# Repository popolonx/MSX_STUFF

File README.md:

# MSX_STUFF
This repository contains:
* Victor VHD IF-C9D replicated card
* NMS82XX front panel freecad files
* panasonic WX/WSX/turbo fdd adapter kicad files
* megaSCSI kicad files
* ToshibaHx34 related (firmware dump + some tcx2001 pinouts)
* etc

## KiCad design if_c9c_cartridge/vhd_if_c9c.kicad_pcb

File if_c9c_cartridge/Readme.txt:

VHD interface for cartridge slot in MSX 1
-Made from reverse engineering IF-C9D card.
-also contains pin headers to connect VHD data extraction pcb
-can be used to play games like Time Gal, Thunder Storm, Road Blaster where the game code is loaded from cassette tape.
-not possible to play games like VROOM and Star Arthur (even though the HW parts are now resolved) as game code is loaded from VHD disk itself and the code is in intermediate language that can be only interpreted by CALL VHD basic extension program.
-only full ROM dump from Victor IF-7900, IF-7910, IF-C9C, or National DA-80F is missing to be able to use CALL VHD basic extension (and thus play VROOM)

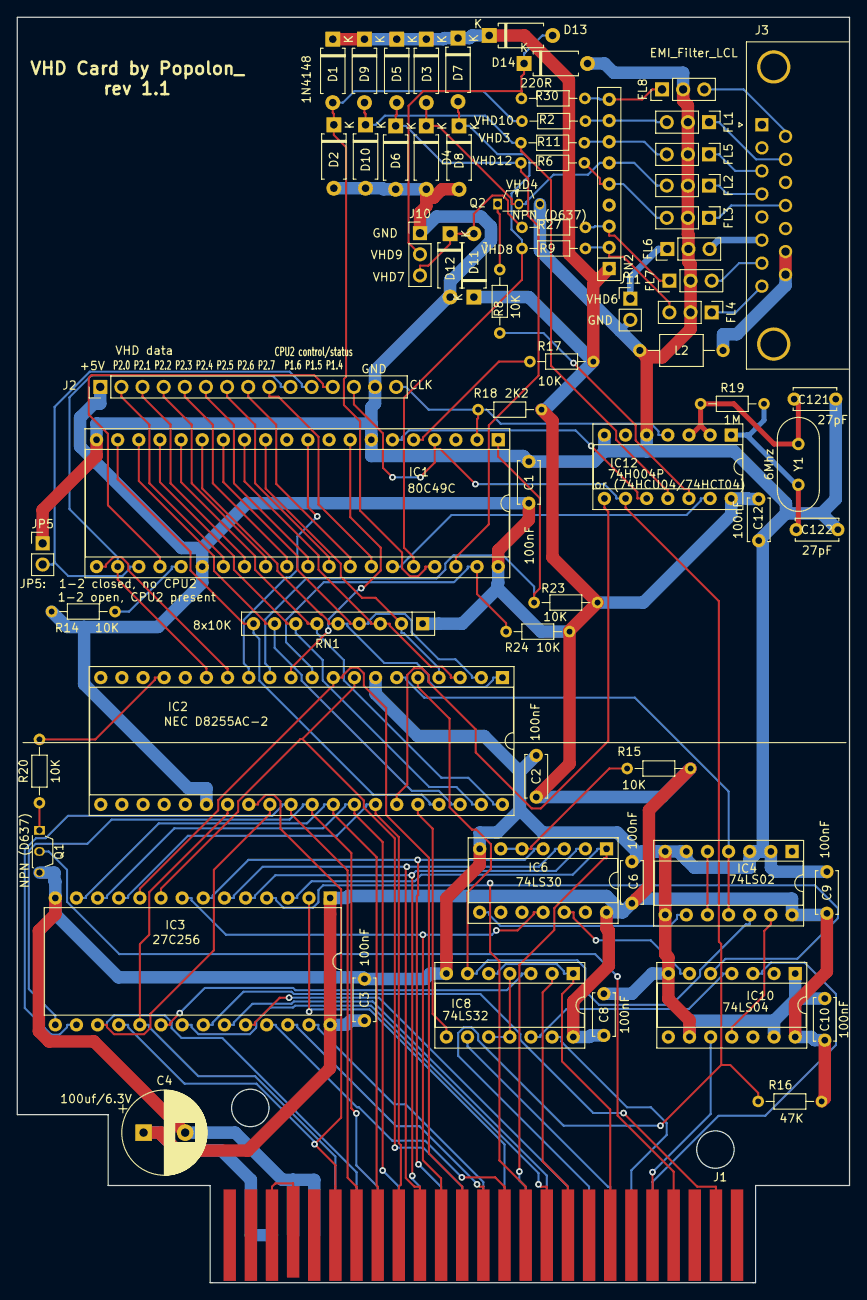
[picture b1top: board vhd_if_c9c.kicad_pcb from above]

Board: 2 copper layers, 100.0 x 152.0 mm, 69 parts (0 on the bottom side), 105 nets.

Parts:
C1, C2, C3, C6, C8, C9, C10, C12: 100nF; C_Disc_D5.0mm_W2.5mm_P5.00mm
C4: 100uf/6.3V; CP_Radial_D10.0mm_P5.00mm
C121, C122: 27pF; C_Disc_D5.0mm_W2.5mm_P5.00mm
D1, D2, D3, D4, D5, D6, D7, D8, D9, D10, D11, D12: 1N4148; D_A-405_P7.62mm_Horizontal
D13, D14: D; D_A-405_P7.62mm_Horizontal
FL1, FL2, FL3, FL4, FL5, FL6, FL7, FL8: EMI_Filter_LCL; PinHeader_1x03_P2.54mm_Vertical
IC1: 80C49C; DIP-40_W15.24mm_Socket
IC2: NEC D8255AC-2; DIP-40_W15.24mm_Socket
IC3: 27C256; DIP-28_W15.24mm
IC4: 74LS02; DIP-14_W7.62mm_Socket
IC6: 74LS30; DIP-14_W7.62mm_Socket
IC8: 74LS32; DIP-14_W7.62mm_Socket
IC10: 74LS04; DIP-14_W7.62mm_Socket
IC12: 74H004P; DIP-14_W7.62mm_Socket
J1: Conn_02x25_Odd_Even; msx_cartridge
J2: CONN_01x15; PinHeader_1x15_P2.54mm_Vertical
J3: DB15_Female; DSUB-15_Female_Horizontal_P2.77x2.84mm_EdgePinOffset7.70mm_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
J10: CONN_01x03; PinHeader_1x03_P2.54mm_Vertical
J11: CONN_01x02; PinHeader_1x02_P2.54mm_Vertical
JP5: Jumper; PinHeader_1x02_P2.54mm_Vertical
L2: L; L_Axial_L5.0mm_D3.6mm_P10.00mm_Horizontal_Murata_BL01RN1A2A2
Q1, Q2: NPN (D637); TO-92S_Wide
R2, R6, R9, R11, R27, R30: 220R; R_Axial_DIN0204_L3.6mm_D1.6mm_P7.62mm_Horizontal
R8, R14, R15, R17, R20, R23, R24: 10K; R_Axial_DIN0204_L3.6mm_D1.6mm_P7.62mm_Horizontal
R16: 47K; R_Axial_DIN0204_L3.6mm_D1.6mm_P7.62mm_Horizontal
R18: 2K2; R_Axial_DIN0204_L3.6mm_D1.6mm_P7.62mm_Horizontal
R19: 1M; R_Axial_DIN0204_L3.6mm_D1.6mm_P7.62mm_Horizontal
RN1: 8x10K; R_Array_SIP9
RN2: 8x4K7; R_Array_SIP9
Y1: 6Mhz; Crystal_HC18-U_Vertical

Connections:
5V: C1.1, C2.1, C3.1, C4.1, C6.1, C8.1, C9.1, C10.1, C12.1, D1.1, D3.1, D5.1, D7.1, D9.1, D11.1, D13.1, IC1.26, IC1.40, IC2.26, IC3.1, IC3.28, IC4.14, IC6.14, IC8.14, IC10.14, IC12.14, J1.45, J1.47, J2.1, R14.1, R15.1, R16.1, R17.1, R18.1, R23.1, R24.1, RN1.1, RN2.1
A0: IC2.9, IC3.10, J1.28
A1: IC2.8, IC3.9, J1.27
A2: IC3.8, IC6.11, J1.30
A3: IC3.7, IC6.4, J1.29
A4: IC3.6, IC6.3, J1.32
A5: IC3.5, IC6.2, J1.31
A6: IC3.4, IC10.5, J1.22
A7: IC3.3, IC6.1, J1.21
A8: IC3.25, J1.24
A9: IC3.24, J1.17
A10: IC3.21, J1.20
A11: IC3.23, J1.19
A12: IC3.2, J1.23
A13: IC3.26, J1.26
A14: IC3.27, J1.25
A15: IC8.2, J1.18
BUSDIR: IC10.10, J1.10
CLK: IC1.2, IC12.4, J2.15, R18.2
CPU2_P1.6: IC1.22, IC2.15, J2.10
D0: IC2.34, IC3.11, J1.34
D1: IC2.33, IC3.12, J1.33
D2: IC2.32, IC3.13, J1.36
D3: IC2.31, IC3.15, J1.35
D4: IC2.30, IC3.16, J1.38
D5: IC2.29, IC3.17, J1.37
D6: IC2.28, IC3.18, J1.40
D7: IC2.27, IC3.19, J1.39
GND: C1.2, C2.2, C3.2, C4.2, C6.2, C8.2, C9.2, C10.2, C12.2, C121.2, C122.2, D2.2, D4.2, D6.2, D8.2, D10.2, D12.2, D14.2, FL1.2, FL2.2, FL3.2, FL4.2, FL5.2, FL6.2, FL7.2, FL8.2, IC1.7, IC1.20, IC2.7, IC3.14, IC4.2, IC4.3, IC4.6, IC4.7, IC4.8, IC6.7, IC8.7, IC10.1, IC10.7, IC10.9, IC10.13, IC12.5, IC12.7, J1.41, J1.43, J2.14, J10.1, J11.2, JP5.1, L2.1, Q1.3, Q2.3
INT01_: J1.8, Q1.2
IOE_: IC8.13, J1.11
LIR_: IC10.3, J1.9
unnamed: C121.1, IC12.2, IC12.3, R19.1, Y1.1
unnamed: C122.1, IC12.1, R19.2, Y1.2
unnamed: D1.2, D2.1, IC1.37, R2.2
unnamed: D5.2, D6.1, IC1.38, R6.2
unnamed: D7.2, D8.1, IC1.36, R9.2
unnamed: D9.2, D10.1, IC12.11, R11.2
unnamed: FL6.3, J3.6
unnamed: FL7.3, J3.7
unnamed: IC1.5, R17.2
unnamed: IC1.6, IC12.10
unnamed: IC1.12, IC2.4, RN1.2
unnamed: IC1.13, IC2.3, RN1.3
unnamed: IC1.14, IC2.2, RN1.4
unnamed: IC1.15, IC2.1, RN1.5
unnamed: IC1.16, IC2.40, RN1.6
unnamed: IC1.17, IC2.39, RN1.7
unnamed: IC1.18, IC2.38, RN1.8
unnamed: IC1.19, IC2.37, RN1.9
unnamed: IC1.25, R14.2
unnamed: IC1.35, IC12.13
unnamed: IC2.5, IC4.12, IC8.6
unnamed: IC2.6, IC4.4, IC4.11
unnamed: IC2.17, R20.2
unnamed: IC2.36, IC8.8
unnamed: IC3.20, IC8.3
unnamed: IC4.9, IC6.8
unnamed: IC4.5, IC4.10
unnamed: IC6.5, IC6.6, R15.2
unnamed: IC8.4, IC8.10, IC8.11
unnamed: IC8.12, IC10.4
unnamed: IC6.12, IC10.6
unnamed: IC4.13, IC10.11
unnamed: IC2.35, IC12.8
unnamed: IC12.12, R8.2
unnamed: J1.44, J1.46
unnamed: J3.14, J3.15, L2.2
unnamed: Q1.1, R20.1
unnamed: Q2.1, R8.1
P1.0_CPU2_P2.0: IC1.27, J2.2
P1.1_CPU2_P2.1: IC1.28, J2.3
P1.2_CPU2_P2.2: IC1.29, J2.4
P1.3_CPU2_P2.3: IC1.30, J2.5
P1.4_CPU2_P2.4: IC1.31, J2.6
P1.5_CPU2_P2.5: IC1.32, J2.7
P1.6_CPU2_P2.6: IC1.33, J2.8
P1.7_CPU2_P2.7: IC1.34, J2.9
P2.0_PC0: IC1.21, IC2.14
P2.2_CPU2_P1.5: IC1.23, J2.11, JP5.2
P2.3_CPU2_P1.4: IC1.24, J2.12
P6: FL6.1, J11.1
P7: D11.2, D12.1, J10.3, R27.1
P9: D13.2, D14.1, J10.2, R30.1
RD_: IC8.1, IC8.5, J1.14
RD_PC6: IC1.8, IC2.11
RESET_: IC1.4, IC12.9, J1.15, J2.13, R16.2
SLOT_: IC3.22, J1.4
T0_PC5: IC1.1, IC2.12, R23.2
T1_PC7: IC1.39, IC2.10, R24.2
VHD3: FL5.1, J3.3
VHD3PULLUP: FL5.3, R11.1, RN2.7
VHD4: FL2.1, J3.4
VHD4PULLUP: D3.2, D4.1, FL2.3, Q2.2, RN2.6
VHD7PULLUP: FL7.1, R27.2, RN2.3
VHD8: FL4.1, J3.8
VHD8PULLUP: FL4.3, R9.1, RN2.2
VHD9: FL8.3, J3.9
VHD9PULLUP: FL8.1, R30.2, RN2.9
VHD10: FL1.1, J3.10
VHD10PULLUP: FL1.3, R2.1, RN2.8
VHD12: FL3.1, J3.12
VHD12PULLUP: FL3.3, R6.1, RN2.5
WR_: IC8.9, J1.13
WR_PC4: IC1.10, IC2.13

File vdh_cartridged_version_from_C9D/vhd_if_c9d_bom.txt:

"Source:"	"E:\msx\vhd_if_c9d_cartversion\vhd_if_c9d.sch"
"Date:"	"30.1.2023 19:45:37"
"Tool:"	"Eeschema (5.1.5)-3"
"Component Count:"	"58"
"Ref"	"Value"	"Part"	"Footprint"	"Description"	"Vendor"
"C1"	"100nF"	"agg-kicad:C"	"Capacitor_THT:C_Disc_D5.0mm_W2.5mm_P5.00mm"	""	""
"C2"	"100nF"	"agg-kicad:C"	"Capacitor_THT:C_Disc_D5.0mm_W2.5mm_P5.00mm"	""	""
"C3"	"100nF"	"agg-kicad:C"	"Capacitor_THT:C_Disc_D5.0mm_W2.5mm_P5.00mm"	""	""
"C4"	"100uf/6.3V"	"Device:CP"	"Capacitor_THT:CP_Radial_D10.0mm_P5.00mm"	"Polarized capacitor"	""
"C6"	"100nF"	"agg-kicad:C"	"Capacitor_THT:C_Disc_D5.0mm_W2.5mm_P5.00mm"	""	""
"C8"	"100nF"	"agg-kicad:C"	"Capacitor_THT:C_Disc_D5.0mm_W2.5mm_P5.00mm"	""	""
"C9"	"100nF"	"agg-kicad:C"	"Capacitor_THT:C_Disc_D5.0mm_W2.5mm_P5.00mm"	""	""
"C10"	"100nF"	"agg-kicad:C"	"Capacitor_THT:C_Disc_D5.0mm_W2.5mm_P5.00mm"	""	""
"C12"	"100nF"	"agg-kicad:C"	"Capacitor_THT:C_Disc_D5.0mm_W2.5mm_P5.00mm"	""	""
"C121"	"27pF"	"agg-kicad:C"	"Capacitor_THT:C_Disc_D5.0mm_W2.5mm_P5.00mm"	""	""
"C122"	"27pF"	"agg-kicad:C"	"Capacitor_THT:C_Disc_D5.0mm_W2.5mm_P5.00mm"	""	""
"D1"	"1N4148"	"agg-kicad:D"	"Diode_THT:D_A-405_P7.62mm_Horizontal"	"Diode"	""
"D2"	"1N4148"	"agg-kicad:D"	"Diode_THT:D_A-405_P7.62mm_Horizontal"	"Diode"	""
"D3"	"1N4148"	"agg-kicad:D"	"Diode_THT:D_A-405_P7.62mm_Horizontal"	"Diode"	""
"D4"	"1N4148"	"agg-kicad:D"	"Diode_THT:D_A-405_P7.62mm_Horizontal"	"Diode"	""
"D5"	"1N4148"	"agg-kicad:D"	"Diode_THT:D_A-405_P7.62mm_Horizontal"	"Diode"	""
"D6"	"1N4148"	"agg-kicad:D"	"Diode_THT:D_A-405_P7.62mm_Horizontal"	"Diode"	""
"D7"	"1N4148"	"agg-kicad:D"	"Diode_THT:D_A-405_P7.62mm_Horizontal"	"Diode"	""
"D8"	"1N4148"	"agg-kicad:D"	"Diode_THT:D_A-405_P7.62mm_Horizontal"	"Diode"	""
"D9"	"1N4148"	"agg-kicad:D"	"Diode_THT:D_A-405_P7.62mm_Horizontal"	"Diode"	""
"D10"	"1N4148"	"agg-kicad:D"	"Diode_THT:D_A-405_P7.62mm_Horizontal"	"Diode"	""
"FL1"	"EMI_Filter_LCL"	"Device:EMI_Filter_LCL"	"Connector_PinHeader_2.54mm:PinHeader_1x03_P2.54mm_Vertical"	"EMI T-filter (LCL)"	""
"FL2"	"EMI_Filter_LCL"	"Device:EMI_Filter_LCL"	"Connector_PinHeader_2.54mm:PinHeader_1x03_P2.54mm_Vertical"	"EMI T-filter (LCL)"	""
"FL3"	"EMI_Filter_LCL"	"Device:EMI_Filter_LCL"	"Connector_PinHeader_2.54mm:PinHeader_1x03_P2.54mm_Vertical"	"EMI T-filter (LCL)"	""
"FL4"	"EMI_Filter_LCL"	"Device:EMI_Filter_LCL"	"Connector_PinHeader_2.54mm:PinHeader_1x03_P2.54mm_Vertical"	"EMI T-filter (LCL)"	""
"FL5"	"EMI_Filter_LCL"	"Device:EMI_Filter_LCL"	"Connector_PinHeader_2.54mm:PinHeader_1x03_P2.54mm_Vertical"	"EMI T-filter (LCL)"	""
"FL6"	"EMI_Filter_LCL"	"Device:EMI_Filter_LCL"	"Connector_PinHeader_2.54mm:PinHeader_1x03_P2.54mm_Vertical"	"EMI T-filter (LCL)"	""
"FL7"	"EMI_Filter_LCL"	"Device:EMI_Filter_LCL"	"Connector_PinHeader_2.54mm:PinHeader_1x03_P2.54mm_Vertical"	"EMI T-filter (LCL)"	""
"IC1"	"P8749C"	"MCU_Intel:8049"	"Package_DIP:DIP-40_W15.24mm_Socket"	"MCS-48 8-bit Microcontroller, 2KB Mask ROM, 128B RAM, DIP-40"	""
"IC2"	"NEC D8255AC-2"	"Interface:8255A"	"Package_DIP:DIP-40_W15.24mm_Socket"	"Programmable Peripheral Interface, PDIP-40"	""
"IC3"	"27C256"	"Memory_EPROM:27C256"	"Package_DIP:DIP-28_W15.24mm"	"OTP EPROM 256 KiBit"	""
"IC6"	"74LS30"	"74xx:74LS30"	"Package_DIP:DIP-14_W7.62mm_Socket"	"8-input NAND"	""
"IC8"	"74LS32"	"74xx:74LS32"	"Package_DIP:DIP-14_W7.62mm_Socket"	"Quad 2-input OR"	""
"IC9"	"74LS02"	"74xx:74LS02"	"Package_DIP:DIP-14_W7.62mm_Socket"	"quad 2-input NOR gate"	""
"IC10"	"74LS04"	"74xx:74LS04"	"Package_DIP:DIP-14_W7.62mm_Socket"	"Hex Inverter"	""
"IC12"	"74H004P or 74HCU04"	"74xx:74HC04"	"Package_DIP:DIP-14_W7.62mm_Socket"	"Hex Inverter"	""
"J1"	"Conn_02x25_Odd_Even"	"Connector_Generic:Conn_02x25_Odd_Even"	"msx cartridge:msx_cartridge"	"Generic connector, double row, 02x25, odd/even pin numbering scheme (row 1 odd numbers, row 2 even numbers), script generated (kicad-library-utils/schlib/autogen/connector/)"	""
"J3"	"DB15_Female"	"Connector:DB15_Female"	"Connector_Dsub:DSUB-15_Female_Horizontal_P2.77x2.84mm_EdgePinOffset7.70mm_Housed_MountingHolesOffset9.12mm"	"15-pin female D-SUB connector (low-density/2 columns)"	""
"L2"	"L"	"agg-kicad:L"	"Inductor_THT:L_Axial_L5.0mm_D3.6mm_P10.00mm_Horizontal_Murata_BL01RN1A2A2"	""	""
"Q1"	"NPN (D637 or BC635)"	"Device:Q_NPN_BCE"	"Package_TO_SOT_THT:TO-92S_Wide"	"NPN transistor, base/collector/emitter"	""
"Q2"	"NPN (D637 or BC635)"	"Device:Q_NPN_BCE"	"Package_TO_SOT_THT:TO-92S_Wide"	"NPN transistor, base/collector/emitter"	""
"R2"	"220R"	"agg-kicad:R"	"Resistor_THT:R_Axial_DIN0204_L3.6mm_D1.6mm_P7.62mm_Horizontal"	""	""
"R6"	"220R"	"agg-kicad:R"	"Resistor_THT:R_Axial_DIN0204_L3.6mm_D1.6mm_P7.62mm_Horizontal"	""	""
"R8"	"10K"	"agg-kicad:R"	"Resistor_THT:R_Axial_DIN0204_L3.6mm_D1.6mm_P7.62mm_Horizontal"	""	""
"R9"	"220R"	"agg-kicad:R"	"Resistor_THT:R_Axial_DIN0204_L3.6mm_D1.6mm_P7.62mm_Horizontal"	""	""
"R11"	"220R"	"agg-kicad:R"	"Resistor_THT:R_Axial_DIN0204_L3.6mm_D1.6mm_P7.62mm_Horizontal"	""	""
"R14"	"10K"	"agg-kicad:R"	"Resistor_THT:R_Axial_DIN0204_L3.6mm_D1.6mm_P7.62mm_Horizontal"	""	""
"R15"	"10K"	"agg-kicad:R"	"Resistor_THT:R_Axial_DIN0204_L3.6mm_D1.6mm_P7.62mm_Horizontal"	""	""
"R16"	"47K"	"agg-kicad:R"	"Resistor_THT:R_Axial_DIN0204_L3.6mm_D1.6mm_P7.62mm_Horizontal"	""	""
"R17"	"10K"	"agg-kicad:R"	"Resistor_THT:R_Axial_DIN0204_L3.6mm_D1.6mm_P7.62mm_Horizontal"	""	""
"R18"	"2K2"	"agg-kicad:R"	"Resistor_THT:R_Axial_DIN0204_L3.6mm_D1.6mm_P7.62mm_Horizontal"	""	""
"R19"	"1M"	"agg-kicad:R"	"Resistor_THT:R_Axial_DIN0204_L3.6mm_D1.6mm_P7.62mm_Horizontal"	""	""
"R20"	"10K"	"agg-kicad:R"	"Resistor_THT:R_Axial_DIN0204_L3.6mm_D1.6mm_P7.62mm_Horizontal"	""	""
"R23"	"10K"	"agg-kicad:R"	"Resistor_THT:R_Axial_DIN0204_L3.6mm_D1.6mm_P7.62mm_Horizontal"	""	""
"R24"	"10K"	"agg-kicad:R"	"Resistor_THT:R_Axial_DIN0204_L3.6mm_D1.6mm_P7.62mm_Horizontal"	""	""
"RN1"	"8x10K"	"Device:R_Network08"	"Resistor_THT:R_Array_SIP9"	"8 resistor network, star topology, bussed resistors, small symbol"	""
"RN2"	"8x4K7"	"Device:R_Network08"	"Resistor_THT:R_Array_SIP9"	"8 resistor network, star topology, bussed resistors, small symbol"	""
"Y1"	"6Mhz"	"Device:Crystal"	"Crystal:Crystal_HC18-U_Vertical"	"Two pin crystal"	""

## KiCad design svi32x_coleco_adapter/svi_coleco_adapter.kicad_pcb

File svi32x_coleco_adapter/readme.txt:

SVI-603 colecovision adapter drawn from pdf schematics:
https://www.samdal.com/SVIDOCS/STM-F_SVI603.pdf
-coleco cartridge connector is using 2.54mm row spacing
-spectravideo side cartridge connector is using 5.08mm row spacing

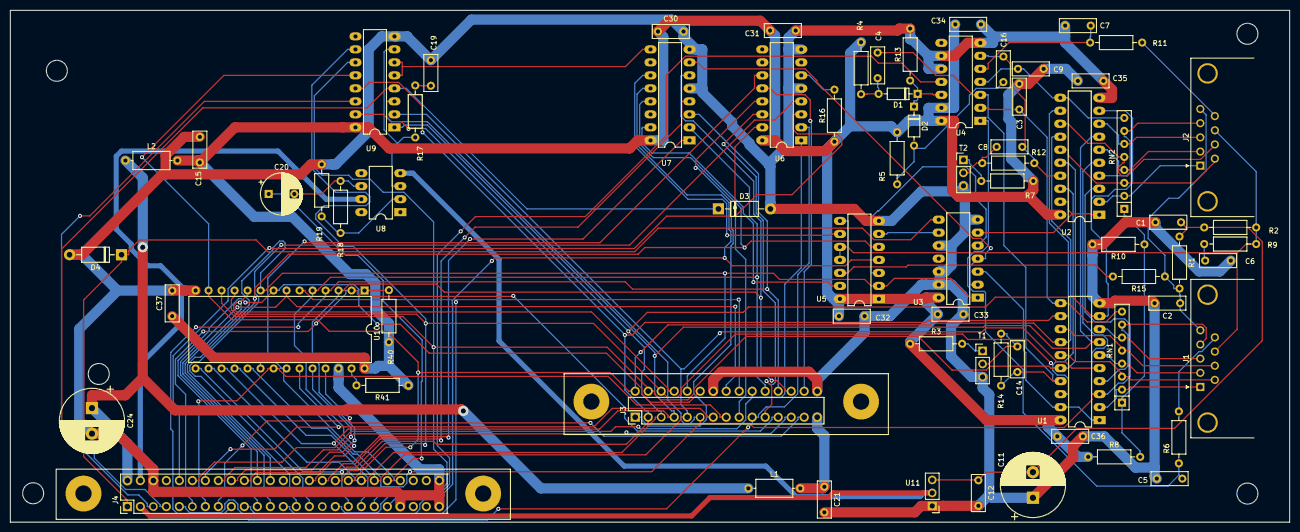
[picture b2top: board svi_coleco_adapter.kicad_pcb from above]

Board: 2 copper layers, 250.0 x 100.0 mm, 72 parts (0 on the bottom side), 93 nets.

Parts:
C1, C5, C7, C19, C30, C31, C32, C33, C34, C35, C36, C37: 100nf; C_Disc_D7.0mm_W2.5mm_P5.00mm
C2, C6: 10nf; C_Disc_D7.0mm_W2.5mm_P5.00mm
C3, C9: 1nF; C_Disc_D7.0mm_W2.5mm_P5.00mm
C4, C16: 10nF; C_Disc_D7.0mm_W2.5mm_P5.00mm
C8, C14: 100pF; C_Disc_D7.0mm_W2.5mm_P5.00mm
C11, C24: 100uf/16v; CP_Radial_D12.5mm_P5.00mm
C12: 100nF; C_Disc_D7.0mm_W2.5mm_P5.00mm
C15, C21: 2.2uf; C_Disc_D7.0mm_W2.5mm_P5.00mm
C20: 4.7uf/16v; CP_Radial_D8.0mm_P5.00mm
D1, D2: 1N4148; D_DO-35_SOD27_P7.62mm_Horizontal
D3: 1N4401; D_DO-41_SOD81_P10.16mm_Horizontal
D4: 1N4001; D_DO-41_SOD81_P10.16mm_Horizontal
J1, J2: Conn_01x09; DSUB-9_Male_Horizontal_P2.77x2.84mm_EdgePinOffset7.70mm_Hou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
J3: COLECO cartridge slot; COLECO_30_PIN_5_02
J4: SVI external bus connector; SVI_50PIN
L1, L2: L; L_Axial_L7.0mm_D3.3mm_P10.16mm_Horizontal_Fastron_MICC
R1, R2, R6, R11: 1K8; R_Axial_DIN0207_L6.3mm_D2.5mm_P10.16mm_Horizontal
R3, R7, R40, R41: 10K; R_Axial_DIN0207_L6.3mm_D2.5mm_P10.16mm_Horizontal
R4, R5: 100K; R_Axial_DIN0207_L6.3mm_D2.5mm_P10.16mm_Horizontal
R8, R10: 270R; R_Axial_DIN0207_L6.3mm_D2.5mm_P10.16mm_Horizontal
R9: 120; R_Axial_DIN0207_L6.3mm_D2.5mm_P10.16mm_Horizontal
R12, R14: 22K; R_Axial_DIN0207_L6.3mm_D2.5mm_P10.16mm_Horizontal
R13: 560R; R_Axial_DIN0207_L6.3mm_D2.5mm_P10.16mm_Horizontal
R15: 250; R_Axial_DIN0207_L6.3mm_D2.5mm_P10.16mm_Horizontal
R16: 3K3; R_Axial_DIN0207_L6.3mm_D2.5mm_P10.16mm_Horizontal
R17: 10R; R_Axial_DIN0207_L6.3mm_D2.5mm_P10.16mm_Horizontal
R18, R19: 2K2; R_Axial_DIN0207_L6.3mm_D2.5mm_P10.16mm_Horizontal
RN1, RN2: 22Kx7; R_Array_SIP8
T1, T2: NPN_CBE_BC547B (was 9014B); PinHeader_1x03_P2.54mm_Vertical
U1, U2: 74LS244; DIP-20_W7.62mm_LongPads
U3: 74LS32; DIP-14_W7.62mm_LongPads
U4, U5: 74LS00; DIP-14_W7.62mm_LongPads
U6, U7: 74LS138; DIP-16_W7.62mm_LongPads
U8: LM741; DIP-8_W7.62mm_LongPads
U9: SN76489; DIP-16_W7.62mm_LongPads
U10: 27C256; DIP-28_W15.24mm
U11: L79L05; PinHeader_1x03_P2.54mm_Vertical

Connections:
5V: C24.1, J4.1, L1.1, L2.1
5V_COL: C21.1, J3.30, L1.2
12V: J4.3, U8.7
+5V: C3.2, C9.2, C15.1, C30.1, C31.1, C32.1, C33.1, C34.1, C35.1, C36.1, C37.1, L2.2, R3.1, R4.1, R5.1, R7.1, R8.1, R16.1, R40.1, R41.1, U1.20, U2.20, U3.14, U4.13, U4.14, U5.1, U5.14, U6.16, U7.16, U9.16, U10.28
A0: J3.7, J4.24, U10.10
A1: J3.9, J4.23, U3.1, U5.2, U10.9
A2: J3.11, J4.22, U10.8
A3: J3.15, J4.21, U10.7
A4: J3.17, J4.20, U10.6
A5: J3.21, J4.19, U7.2, U10.5
A6: J3.23, J4.18, U7.3, U10.4
A7: J3.25, J4.17, U7.6, U10.3
A8: J3.28, J4.16, U10.25
A9: J3.26, J4.15, U10.24
A10: J3.16, J4.14, U10.21
A11: J3.14, J4.13, U10.23
A12: J3.24, J4.12, U10.2
A13: J3.19, J4.11, U6.1
A14: J3.20, J4.10, U6.2
A15: J4.9, U6.3
CLK: J4.8, U9.14
COL_JOY5: C2.1, J1.5, J2.5, R1.2, R15.1
COL_JOY8: J1.8, J2.8, R2.2, R9.1, U5.10, U5.11
CSOUND: C20.1, J4.41
CS_8000: J3.18, U6.15
CS_A000: J3.22, U6.14
CS_C000: J3.2, U6.13
CS_E000: J3.27, U6.12
D0: J3.5, J4.33, U1.18, U2.18, U9.10, U10.11
D1: J3.3, J4.34, U1.16, U2.16, U9.11, U10.12
D2: J3.1, J4.35, U1.14, U2.14, U9.12, U10.13
D3: J3.4, J4.36, U1.12, U2.12, U9.13, U10.15
D4: J3.6, J4.37, U1.9, U2.9, U9.15, U10.16
D5: J3.8, J4.38, U1.7, U2.7, U9.1, U10.17
D6: J3.10, J4.39, U1.5, U2.5, U9.2, U10.18
D7: J3.12, J4.40, U1.3, U2.3, U9.3, U10.19
GND: C1.2, C2.2, C5.1, C6.2, C7.1, C11.1, C12.2, C15.2, C19.2, C21.2, C24.2, C30.2, C31.2, C32.2, C33.2, C34.2, C35.2, C36.2, C37.2, D3.2, D4.2, J3.13, J3.29, J4.5, J4.44, J4.49, J4.50, R10.2, R13.2, R19.2, T1.3, T2.3, U1.10, U2.10, U3.7, U3.10, U3.12, U3.13, U4.7, U4.9, U4.10, U5.7, U6.5, U6.8, U7.5, U7.8, U9.8, U10.14, U10.26, U11.1
J1_ENABLE: U1.1, U1.19, U3.3
J2_ENABLE: U2.1, U2.19, U3.6
MINUS12V: J4.4, U8.4, U11.2
unnamed: C1.1, C11.2, C12.1, R1.1, R2.1, U11.3
unnamed: C3.1, RN1.8, U1.11, U4.2
unnamed: C4.2, D1.2, R4.2
unnamed: C5.2, R6.2, U4.1
unnamed: C6.1, R9.2
unnamed: C7.2, R11.2, U4.5
unnamed: C8.2, R12.2, T2.2
unnamed: C9.1, RN2.8, U2.11, U4.4
unnamed: C4.1, C14.1, R14.1, U1.17, U4.3
unnamed: C14.2, R14.2, T1.2
unnamed: C8.1, C16.1, R12.1, U2.17, U4.6
unnamed: C16.2, D2.2, R5.2
unnamed: C19.1, R17.2
unnamed: C20.2, R18.2, U8.6
unnamed: D1.1, D2.1, R13.1, U4.12
unnamed: J1.1, RN1.2, U1.2
unnamed: J1.2, RN1.4, U1.6
unnamed: J1.3, RN1.6, U1.8
unnamed: J1.4, RN1.7, U1.4
unnamed: J1.6, RN1.3, U1.15
unnamed: J1.7, RN1.5, U1.13
unnamed: J1.9, R6.1
unnamed: J2.1, RN2.2, U2.2
unnamed: J2.2, RN2.4, U2.6
unnamed: J2.3, RN2.6, U2.8
unnamed: J2.4, RN2.7, U2.4
unnamed: J2.6, RN2.3, U2.15
unnamed: J2.7, RN2.5, U2.13
unnamed: J2.9, R11.1
unnamed: R3.2, T1.1
unnamed: R7.2, T2.1
unnamed: R8.2, R10.1, RN1.1, RN2.1
unnamed: R15.2, U5.8, U5.12
unnamed: R16.2, U6.6
unnamed: R17.1, U8.3, U9.7
unnamed: R18.1, R19.1, U8.2
unnamed: R40.2, U10.1
unnamed: R41.2, U10.27
unnamed: U3.5, U5.3
unnamed: U3.9, U5.6
unnamed: U5.9, U7.11
unnamed: U5.13, U7.15
unnamed: U7.9, U9.5, U9.6
SKEN: U3.2, U3.4, U7.7
_CNTRL2: D4.1, J4.2, U3.8
_EXCSR: J4.26, U5.4, U7.12
_EXCSW: J4.28, U5.5, U7.13
_INT: J4.42, U4.11
_IORQ: J4.31, U7.4
_MREQ: J4.30, U6.4
_RAMDIS: J4.43, U6.11, U10.20, U10.22
_WAIT: D3.1, J4.6, U9.4
_WR: J4.29, U7.1

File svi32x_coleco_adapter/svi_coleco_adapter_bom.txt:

Reference, Value, Footprint, Datasheet
"U5","74LS00","Package_DIP:DIP-14_W7.62mm_LongPads","http://www.ti.com/lit/gpn/sn74ls00"
"U4","74LS00","Package_DIP:DIP-14_W7.62mm_LongPads","http://www.ti.com/lit/gpn/sn74ls00"
"U3","74LS32","Package_DIP:DIP-14_W7.62mm_LongPads",""
"U7","74LS138","Package_DIP:DIP-16_W7.62mm_LongPads",""
"U6","74LS138","Package_DIP:DIP-16_W7.62mm_LongPads",""
"U10","27C256","Package_DIP:DIP-28_W15.24mm","http://ww1.microchip.com/downloads/en/DeviceDoc/11107M.pdf"
"J4","SVI external bus connector","Connector:SVI_50PIN","" 5.08mm row spacing
"J3","COLECO cartridge slot","Connector:COLECO_30_PIN"," 2.54mm row spacing
"J2","Conn_01x09","Connector_Dsub:DSUB-9_Male_Horizontal_P2.77x2.84mm_EdgePinOffset7.70mm_Housed_MountingHolesOffset9.12mm","~"
"J1","Conn_01x09","Connector_Dsub:DSUB-9_Male_Horizontal_P2.77x2.84mm_EdgePinOffset7.70mm_Housed_MountingHolesOffset9.12mm","~"
"R16","3K3","Resistor_THT:R_Axial_DIN0207_L6.3mm_D2.5mm_P10.16mm_Horizontal",""
"D4","1N4001","Diode_THT:D_DO-41_SOD81_P10.16mm_Horizontal","http://www.vishay.com/docs/88503/1n4001.pdf"
"C24","100uf/16v","Capacitor_THT:CP_Radial_D12.5mm_P5.00mm","~"
"C15","2.2uf","Capacitor_THT:C_Disc_D7.0mm_W2.5mm_P5.00mm",""
"C21","2.2uf","Capacitor_THT:C_Disc_D7.0mm_W2.5mm_P5.00mm",""
"L2","L","Inductor_THT:L_Axial_L7.0mm_D3.3mm_P10.16mm_Horizontal_Fastron_MICC",""
"L1","L","Inductor_THT:L_Axial_L7.0mm_D3.3mm_P10.16mm_Horizontal_Fastron_MICC",""
"U11","L79L05","Connector_PinHeader_2.54mm:PinHeader_1x03_P2.54mm_Vertical",""
"C12","100nF","Capacitor_THT:C_Disc_D7.0mm_W2.5mm_P5.00mm",""
"C11","100uf/16v","Capacitor_THT:CP_Radial_D12.5mm_P5.00mm","~"
"R2","1K8","Resistor_THT:R_Axial_DIN0207_L6.3mm_D2.5mm_P10.16mm_Horizontal",""
"R1","1K8","Resistor_THT:R_Axial_DIN0207_L6.3mm_D2.5mm_P10.16mm_Horizontal",""
"R9","120","Resistor_THT:R_Axial_DIN0207_L6.3mm_D2.5mm_P10.16mm_Horizontal",""
"R15","250","Resistor_THT:R_Axial_DIN0207_L6.3mm_D2.5mm_P10.16mm_Horizontal",""
"C6","10nf","Capacitor_THT:C_Disc_D7.0mm_W2.5mm_P5.00mm",""
"C2","10nf","Capacitor_THT:C_Disc_D7.0mm_W2.5mm_P5.00mm",""
"C1","100nf","Capacitor_THT:C_Disc_D7.0mm_W2.5mm_P5.00mm",""
"U9","SN76489","Package_DIP:DIP-16_W7.62mm_LongPads",""
"U1","74LS244","Package_DIP:DIP-20_W7.62mm_LongPads","http://www.ti.com/lit/gpn/sn74LS244"
"U2","74LS244","Package_DIP:DIP-20_W7.62mm_LongPads","http://www.ti.com/lit/gpn/sn74LS244"
"R10","270R","Resistor_THT:R_Axial_DIN0207_L6.3mm_D2.5mm_P10.16mm_Horizontal",""
"R8","270R","Resistor_THT:R_Axial_DIN0207_L6.3mm_D2.5mm_P10.16mm_Horizontal",""
"RN1","22Kx7","Resistor_THT:R_Array_SIP8","http://www.vishay.com/docs/31509/csc.pdf"
"RN2","22Kx7","Resistor_THT:R_Array_SIP8","http://www.vishay.com/docs/31509/csc.pdf"
"R6","1K8","Resistor_THT:R_Axial_DIN0207_L6.3mm_D2.5mm_P10.16mm_Horizontal",""
"C5","100nf","Capacitor_THT:C_Disc_D7.0mm_W2.5mm_P5.00mm",""
"R11","1K8","Resistor_THT:R_Axial_DIN0207_L6.3mm_D2.5mm_P10.16mm_Horizontal",""
"C7","100nf","Capacitor_THT:C_Disc_D7.0mm_W2.5mm_P5.00mm",""
"U8","LM741","Package_DIP:DIP-8_W7.62mm_LongPads","http://www.ti.com/lit/ds/symlink/lm741.pdf"
"R17","10R","Resistor_THT:R_Axial_DIN0207_L6.3mm_D2.5mm_P10.16mm_Horizontal",""
"C19","100nf","Capacitor_THT:C_Disc_D7.0mm_W2.5mm_P5.00mm",""
"R19","2K2","Resistor_THT:R_Axial_DIN0207_L6.3mm_D2.5mm_P10.16mm_Horizontal",""
"R18","2K2","Resistor_THT:R_Axial_DIN0207_L6.3mm_D2.5mm_P10.16mm_Horizontal",""
"C20","4.7uf/16v","Capacitor_THT:CP_Radial_D8.0mm_P5.00mm","~"
"T1","NPN_CBE_BC547B (was 9014B)","Connector_PinHeader_2.54mm:PinHeader_1x03_P2.54mm_Vertical","~"
"T2","NPN_CBE_BC547B  (was 9014B)","Connector_PinHeader_2.54mm:PinHeader_1x03_P2.54mm_Vertical","~"
"R7","10K","Resistor_THT:R_Axial_DIN0207_L6.3mm_D2.5mm_P10.16mm_Horizontal",""
"R3","10K","Resistor_THT:R_Axial_DIN0207_L6.3mm_D2.5mm_P10.16mm_Horizontal",""
"R14","22K","Resistor_THT:R_Axial_DIN0207_L6.3mm_D2.5mm_P10.16mm_Horizontal",""
"R12","22K","Resistor_THT:R_Axial_DIN0207_L6.3mm_D2.5mm_P10.16mm_Horizontal",""
"C14","100pF","Capacitor_THT:C_Disc_D7.0mm_W2.5mm_P5.00mm",""
"C8","100pF","Capacitor_THT:C_Disc_D7.0mm_W2.5mm_P5.00mm",""
"C16","10nF","Capacitor_THT:C_Disc_D7.0mm_W2.5mm_P5.00mm",""
"R5","100K","Resistor_THT:R_Axial_DIN0207_L6.3mm_D2.5mm_P10.16mm_Horizontal",""
"D2","1N4148","Diode_THT:D_DO-35_SOD27_P7.62mm_Horizontal","https://assets.nexperia.com/documents/data-sheet/1N4148_1N4448.pdf"
"R13","560R","Resistor_THT:R_Axial_DIN0207_L6.3mm_D2.5mm_P10.16mm_Horizontal",""
"D1","1N4148","Diode_THT:D_DO-35_SOD27_P7.62mm_Horizontal","https://assets.nexperia.com/documents/data-sheet/1N4148_1N4448.pdf"
"R4","100K","Resistor_THT:R_Axial_DIN0207_L6.3mm_D2.5mm_P10.16mm_Horizontal",""
"C4","10nF","Capacitor_THT:C_Disc_D7.0mm_W2.5mm_P5.00mm",""
"C9","1nF","Capacitor_THT:C_Disc_D7.0mm_W2.5mm_P5.00mm",""
"C3","1nF","Capacitor_THT:C_Disc_D7.0mm_W2.5mm_P5.00mm",""
"D3","1N4401","Zener Diode 7.5v_THT:D_DO-41_SOD81_P10.16mm_Horizontal","http://www.vishay.com/docs/88503/1n4001.pdf"
"C30","100nf","Capacitor_THT:C_Disc_D7.0mm_W2.5mm_P5.00mm",""
"C31","100nf","Capacitor_THT:C_Disc_D7.0mm_W2.5mm_P5.00mm",""
"C32","100nf","Capacitor_THT:C_Disc_D7.0mm_W2.5mm_P5.00mm",""
"C33","100nf","Capacitor_THT:C_Disc_D7.0mm_W2.5mm_P5.00mm",""
"C34","100nf","Capacitor_THT:C_Disc_D7.0mm_W2.5mm_P5.00mm",""
"C35","100nf","Capacitor_THT:C_Disc_D7.0mm_W2.5mm_P5.00mm",""
"C36","100nf","Capacitor_THT:C_Disc_D7.0mm_W2.5mm_P5.00mm",""
"C37","100nf","Capacitor_THT:C_Disc_D7.0mm_W2.5mm_P5.00mm",""
"R40","10K","Resistor_THT:R_Axial_DIN0207_L6.3mm_D2.5mm_P10.16mm_Horizontal",""
"R41","10K","Resistor_THT:R_Axial_DIN0207_L6.3mm_D2.5mm_P10.16mm_Horizontal",""

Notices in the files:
vhd_c9d_card/victor_if_c9d_80c49c_2k_rom_some_comments.asm:
(c) Copyright 1996-2003 Conquest Consultants
